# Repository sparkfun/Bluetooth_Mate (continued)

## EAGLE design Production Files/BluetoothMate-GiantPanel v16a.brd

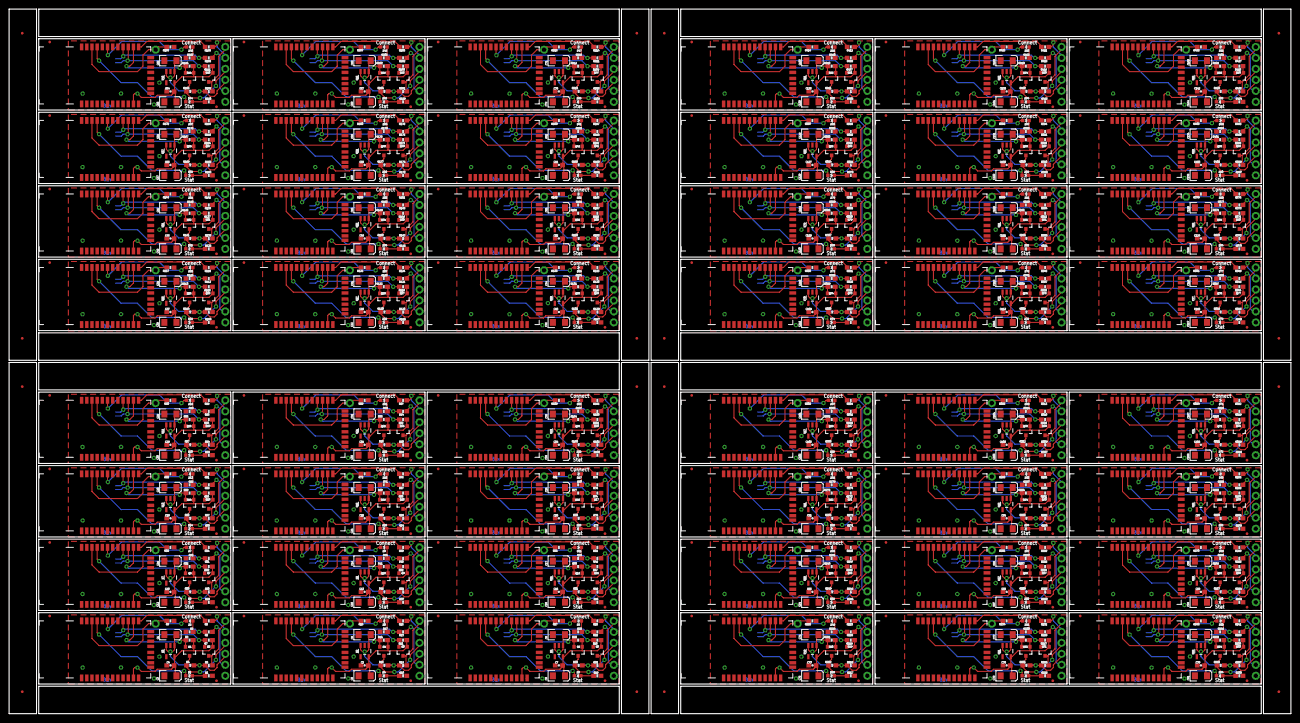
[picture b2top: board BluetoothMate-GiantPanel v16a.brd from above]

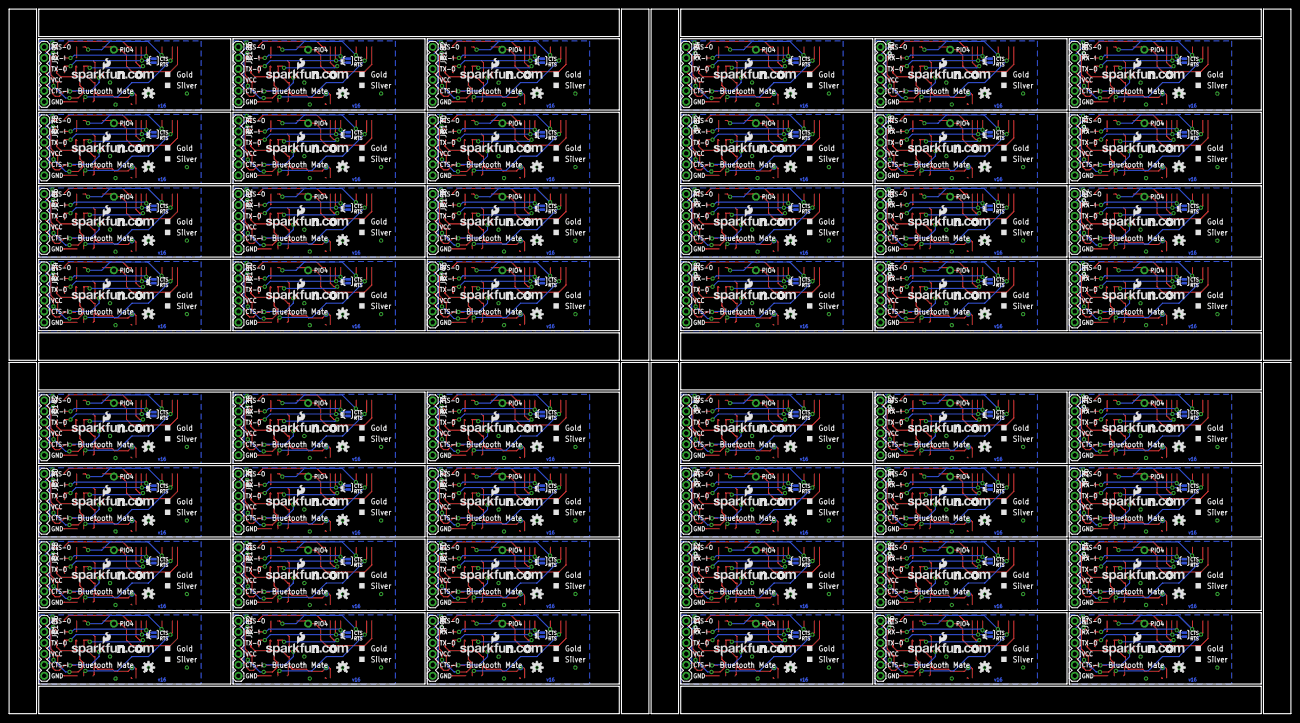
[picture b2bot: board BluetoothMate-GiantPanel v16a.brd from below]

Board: 2 copper layers, 296.7 x 163.1 mm, 1264 parts (240 on the bottom side), 768 nets.

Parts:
C1, C3, C5, C6, C8, C9, C11, C12, C14, C15, C17, C18, C20, C21, C23, C24, C26, C27, C29, C30, C32, C33, C35, C36, C38, C39, C41, C42, C44, C45, C47, C48, C50, C51, C53, C54, C56, C57, C59, C60, C62, C63, C65, C66, C68, C69, C71, C72, C74, C75, C77, C78, C80, C81, C83, C84, C86, C87, C89, C90, C92, C93, C95, C96, C98, C99, C101, C102, C104, C105, C107, C108, C110, C111, C113, C114, C116, C117, C119, C120, C122, C123, C125, C126, C128, C129, C131, C132, C134, C135, C137, C138, C140, C141, C143, C144: 10uF; EIA3216
C2, C4, C7, C10, C13, C16, C19, C22, C25, C28, C31, C34, C37, C40, C43, C46, C49, C52, C55, C58, C61, C64, C67, C70, C73, C76, C79, C82, C85, C88, C91, C94, C97, C100, C103, C106, C109, C112, C115, C118, C121, C124, C127, C130, C133, C136, C139, C142: 1uF; 0603-CAP
D1, D4, D6, D8, D10, D12, D14, D16, D18, D20, D22, D24, D26, D28, D30, D32, D34, D36, D38, D40, D42, D44, D46, D48, D50, D52, D54, D56, D58, D60, D62, D64, D66, D68, D70, D72, D74, D76, D78, D80, D82, D84, D86, D88, D90, D92, D94, D96: Red; LED-0603
D2, D3, D5, D7, D9, D11, D13, D15, D17, D19, D21, D23, D25, D27, D29, D31, D33, D35, D37, D39, D41, D43, D45, D47, D49, D51, D53, D55, D57, D59, D61, D63, D65, D67, D69, D71, D73, D75, D77, D79, D81, D83, D85, D87, D89, D91, D93, D95: Green; LED-0603
E$1, E$2, E$3, E$4, E$5, E$6, E$7, E$8, E$9, E$10, E$11, E$12, E$13, E$14, E$15, E$16: MICRO-FIDUCIAL
JP1, JP4, JP7, JP8, JP11, JP12, JP15, JP16, JP19, JP20, JP23, JP24, JP27, JP28, JP31, JP32, JP35, JP36, JP39, JP40, JP43, JP44, JP47, JP48, JP51, JP52, JP55, JP56, JP59, JP60, JP63, JP64, JP67, JP68, JP71, JP72, JP75, JP76, JP79, JP80, JP83, JP84, JP87, JP88, JP91, JP92, JP95, JP96, JP99, JP100, JP103, JP104, JP107, JP108, JP111, JP112, JP115, JP116, JP119, JP120, JP123, JP124, JP127, JP128, JP131, JP132, JP135, JP136, JP139, JP140, JP143, JP144, JP147, JP148, JP151, JP152, JP155, JP156, JP159, JP160, JP163, JP164, JP167, JP168, JP171, JP172, JP175, JP176, JP179, JP180, JP183, JP184, JP187, JP188, JP191, JP192: FIDUCIAL1X2.5; FIDUCIAL-1X2.5
JP2, JP5, JP9, JP13, JP17, JP21, JP25, JP29, JP33, JP37, JP41, JP45, JP49, JP53, JP57, JP61, JP65, JP69, JP73, JP77, JP81, JP85, JP89, JP93, JP97, JP101, JP105, JP109, JP113, JP117, JP121, JP125, JP129, JP133, JP137, JP141, JP145, JP149, JP153, JP157, JP161, JP165, JP169, JP173, JP177, JP181, JP185, JP189: M01SMDNS; 1X01NS
JP3, JP6, JP10, JP14, JP18, JP22, JP26, JP30, JP34, JP38, JP42, JP46, JP50, JP54, JP58, JP62, JP66, JP70, JP74, JP78, JP82, JP86, JP90, JP94, JP98, JP102, JP106, JP110, JP114, JP118, JP122, JP126, JP130, JP134, JP138, JP142, JP146, JP150, JP154, JP158, JP162, JP166, JP170, JP174, JP178, JP182, JP186, JP190: 1X06
LOGO1, LOGO2, LOGO3, LOGO4, LOGO5, LOGO6, LOGO7, LOGO8, LOGO9, LOGO10, LOGO11, LOGO12, LOGO13, LOGO14, LOGO15, LOGO16, LOGO17, LOGO18, LOGO19, LOGO20, LOGO21, LOGO22, LOGO23, LOGO24, LOGO25, LOGO26, LOGO27, LOGO28, LOGO29, LOGO30, LOGO31, LOGO32, LOGO33, LOGO34, LOGO35, LOGO36, LOGO37, LOGO38, LOGO39, LOGO40, LOGO41, LOGO42, LOGO43, LOGO44, LOGO45, LOGO46, LOGO47, LOGO48: OSHW-LOGOS; OSHW-LOGO-S
Q1, Q2, Q3, Q4, Q5, Q6, Q7, Q8, Q9, Q10, Q11, Q12, Q13, Q14, Q15, Q16, Q17, Q18, Q19, Q20, Q21, Q22, Q23, Q24, Q25, Q26, Q27, Q28, Q29, Q30, Q31, Q32, Q33, Q34, Q35, Q36, Q37, Q38, Q39, Q40, Q41, Q42, Q43, Q44, Q45, Q46, Q47, Q48, Q49, Q50, Q51, Q52, Q53, Q54, Q55, Q56, Q57, Q58, Q59, Q60, Q61, Q62, Q63, Q64, Q65, Q66, Q67, Q68, Q69, Q70, Q71, Q72, Q73, Q74, Q75, Q76, Q77, Q78, Q79, Q80, Q81, Q82, Q83, Q84, Q85, Q86, Q87, Q88, Q89, Q90, Q91, Q92, Q93, Q94, Q95, Q96: MOSFET-NCHANNELSMD; SOT23-3
R1, R6, R10, R17, R19, R26, R28, R35, R37, R44, R46, R53, R55, R62, R64, R71, R73, R80, R82, R89, R91, R98, R100, R107, R109, R116, R118, R125, R127, R134, R136, R143, R145, R152, R154, R161, R163, R170, R172, R179, R181, R188, R190, R197, R199, R206, R208, R215, R217, R224, R226, R233, R235, R242, R244, R251, R253, R260, R262, R269, R271, R278, R280, R287, R289, R296, R298, R305, R307, R314, R316, R323, R325, R332, R334, R341, R343, R350, R352, R359, R361, R368, R370, R377, R379, R386, R388, R395, R397, R404, R406, R413, R415, R422, R424, R431: 330; 0603-RES
R2, R3, R4, R5, R7, R8, R9, R11, R12, R13, R14, R15, R16, R18, R20, R21, R22, R23, R24, R25, R27, R29, R30, R31, R32, R33, R34, R36, R38, R39, R40, R41, R42, R43, R45, R47, R48, R49, R50, R51, R52, R54, R56, R57, R58, R59, R60, R61, R63, R65, R66, R67, R68, R69, R70, R72, R74, R75, R76, R77, R78, R79, R81, R83, R84, R85, R86, R87, R88, R90, R92, R93, R94, R95, R96, R97, R99, R101, R102, R103, R104, R105, R106, R108, R110, R111, R112, R113, R114, R115, R117, R119, R120, R121, R122, R123, R124, R126, R128, R129, R130, R131, R132, R133, R135, R137, R138, R139, R140, R141, R142, R144, R146, R147, R148, R149, R150, R151, R153, R155, R156, R157, R158, R159, R160, R162, R164, R165, R166, R167, R168, R169, R171, R173, R174, R175, R176, R177, R178, R180, R182, R183, R184, R185, R186, R187, R189, R191, R192, R193, R194, R195, R196, R198, R200, R201, R202, R203, R204, R205, R207, R209, R210, R211, R212, R213, R214, R216, R218, R219, R220, R221, R222, R223, R225, R227, R228, R229, R230, R231, R232, R234, R236, R237, R238, R239, R240, R241, R243, R245, R246, R247, R248, R249, R250, R252, R254, R255, R256, R257, R258, R259, R261, R263, R264, R265, R266, R267, R268, R270, R272, R273, R274, R275, R276, R277, R279, R281, R282, R283, R284, R285, R286, R288, R290, R291, R292, R293, R294, R295, R297, R299, R300, R301, R302, R303, R304, R306, R308, R309, R310, R311, R312, R313, R315, R317, R318, R319, R320, R321, R322, R324, R326, R327, R328, R329, R330, R331, R333, R335, R336, R337, R338, R339, R340, R342, R344, R345, R346, R347, R348, R349, R351, R353, R354, R355, R356, R357, R358, R360, R362, R363, R364, R365, R366, R367, R369, R371, R372, R373, R374, R375, R376, R378, R380, R381, R382, R383, R384, R385, R387, R389, R390, R391, R392, R393, R394, R396, R398, R399, R400, R401, R402, R403, R405, R407, R408, R409, R410, R411, R412, R414, R416, R417, R418, R419, R420, R421, R423, R425, R426, R427, R428, R429, R430, R432: 10K; 0603-RES
SJ1, SJ2, SJ3, SJ4, SJ5, SJ6, SJ7, SJ8, SJ9, SJ10, SJ11, SJ12, SJ13, SJ14, SJ15, SJ16, SJ17, SJ18, SJ19, SJ20, SJ21, SJ22, SJ23, SJ24, SJ25, SJ26, SJ27, SJ28, SJ29, SJ30, SJ31, SJ32, SJ33, SJ34, SJ35, SJ36, SJ37, SJ38, SJ39, SJ40, SJ41, SJ42, SJ43, SJ44, SJ45, SJ46, SJ47, SJ48: SOLDERJUMPERNO; SJ_2S-NO
TP1, TP2, TP3, TP4, TP5, TP6, TP7, TP8, TP9, TP10, TP11, TP12, TP13, TP14, TP15, TP16, TP17, TP18, TP19, TP20, TP21, TP22, TP23, TP24, TP25, TP26, TP27, TP28, TP29, TP30, TP31, TP32, TP33, TP34, TP35, TP36, TP37, TP38, TP39, TP40, TP41, TP42, TP43, TP44, TP45, TP46, TP47, TP48: PAD.03X.05
U1, U4, U6, U8, U10, U12, U14, U16, U18, U20, U22, U24, U26, U28, U30, U32, U34, U36, U38, U40, U42, U44, U46, U48, U50, U52, U54, U56, U58, U60, U62, U64, U66, U68, U70, U72, U74, U76, U78, U80, U82, U84, U86, U88, U90, U92, U94, U96: BLUETOOTH-RN41; RN41
U2, U3, U5, U7, U9, U11, U13, U15, U17, U19, U21, U23, U25, U27, U29, U31, U33, U35, U37, U39, U41, U43, U45, U47, U49, U51, U53, U55, U57, U59, U61, U63, U65, U67, U69, U71, U73, U75, U77, U79, U81, U83, U85, U87, U89, U91, U93, U95: V_REG_LDOSMD; SOT23-5
U$1, U$2, U$3, U$4, U$5, U$6, U$7, U$8, U$9, U$10, U$11, U$12, U$13, U$14, U$15, U$16, U$17, U$18, U$19, U$20, U$21, U$22, U$23, U$24, U$25, U$26, U$27, U$28, U$29, U$30, U$31, U$32, U$33, U$34, U$35, U$36, U$37, U$38, U$39, U$40, U$41, U$42, U$43, U$44, U$45, U$46, U$47, U$48: LOGO-SFENEW; SFE-NEW-WEBLOGO

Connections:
3.3V: C3.A, C4.1, Q1.1, Q2.1, R3.1, R7.1, TP1.P$1, U1.11, U3.5
3.3V1: C2.1, C6.A, Q3.1, Q4.1, R11.1, R14.1, TP2.P$1, U2.5, U4.11
3.3V2: C7.1, C9.A, Q5.1, Q6.1, R20.1, R23.1, TP3.P$1, U5.5, U6.11
3.3V3: C10.1, C12.A, Q7.1, Q8.1, R29.1, R32.1, TP4.P$1, U7.5, U8.11
3.3V4: C13.1, C15.A, Q9.1, Q10.1, R38.1, R41.1, TP5.P$1, U9.5, U10.11
3.3V5: C16.1, C18.A, Q11.1, Q12.1, R47.1, R50.1, TP6.P$1, U11.5, U12.11
3.3V6: C19.1, C21.A, Q13.1, Q14.1, R56.1, R59.1, TP7.P$1, U13.5, U14.11
3.3V7: C22.1, C24.A, Q15.1, Q16.1, R65.1, R68.1, TP8.P$1, U15.5, U16.11
3.3V8: C25.1, C27.A, Q17.1, Q18.1, R74.1, R77.1, TP9.P$1, U17.5, U18.11
3.3V9: C28.1, C30.A, Q19.1, Q20.1, R83.1, R86.1, TP10.P$1, U19.5, U20.11
3.3V10: C31.1, C33.A, Q21.1, Q22.1, R92.1, R95.1, TP11.P$1, U21.5, U22.11
3.3V11: C34.1, C36.A, Q23.1, Q24.1, R101.1, R104.1, TP12.P$1, U23.5, U24.11
3.3V12: C37.1, C39.A, Q25.1, Q26.1, R110.1, R113.1, TP13.P$1, U25.5, U26.11
3.3V13: C40.1, C42.A, Q27.1, Q28.1, R119.1, R122.1, TP14.P$1, U27.5, U28.11
3.3V14: C43.1, C45.A, Q29.1, Q30.1, R128.1, R131.1, TP15.P$1, U29.5, U30.11
3.3V15: C46.1, C48.A, Q31.1, Q32.1, R137.1, R140.1, TP16.P$1, U31.5, U32.11
3.3V16: C49.1, C51.A, Q33.1, Q34.1, R146.1, R149.1, TP17.P$1, U33.5, U34.11
3.3V17: C52.1, C54.A, Q35.1, Q36.1, R155.1, R158.1, TP18.P$1, U35.5, U36.11
3.3V18: C55.1, C57.A, Q37.1, Q38.1, R164.1, R167.1, TP19.P$1, U37.5, U38.11
3.3V19: C58.1, C60.A, Q39.1, Q40.1, R173.1, R176.1, TP20.P$1, U39.5, U40.11
3.3V20: C61.1, C63.A, Q41.1, Q42.1, R182.1, R185.1, TP21.P$1, U41.5, U42.11
3.3V21: C64.1, C66.A, Q43.1, Q44.1, R191.1, R194.1, TP22.P$1, U43.5, U44.11
3.3V22: C67.1, C69.A, Q45.1, Q46.1, R200.1, R203.1, TP23.P$1, U45.5, U46.11
3.3V23: C70.1, C72.A, Q47.1, Q48.1, R209.1, R212.1, TP24.P$1, U47.5, U48.11
3.3V24: C73.1, C75.A, Q49.1, Q50.1, R218.1, R221.1, TP25.P$1, U49.5, U50.11
3.3V25: C76.1, C78.A, Q51.1, Q52.1, R227.1, R230.1, TP26.P$1, U51.5, U52.11
3.3V26: C79.1, C81.A, Q53.1, Q54.1, R236.1, R239.1, TP27.P$1, U53.5, U54.11
3.3V27: C82.1, C84.A, Q55.1, Q56.1, R245.1, R248.1, TP28.P$1, U55.5, U56.11
3.3V28: C85.1, C87.A, Q57.1, Q58.1, R254.1, R257.1, TP29.P$1, U57.5, U58.11
3.3V29: C88.1, C90.A, Q59.1, Q60.1, R263.1, R266.1, TP30.P$1, U59.5, U60.11
3.3V30: C91.1, C93.A, Q61.1, Q62.1, R272.1, R275.1, TP31.P$1, U61.5, U62.11
3.3V31: C94.1, C96.A, Q63.1, Q64.1, R281.1, R284.1, TP32.P$1, U63.5, U64.11
3.3V32: C97.1, C99.A, Q65.1, Q66.1, R290.1, R293.1, TP33.P$1, U65.5, U66.11
3.3V33: C100.1, C102.A, Q67.1, Q68.1, R299.1, R302.1, TP34.P$1, U67.5, U68.11
3.3V34: C103.1, C105.A, Q69.1, Q70.1, R308.1, R311.1, TP35.P$1, U69.5, U70.11
3.3V35: C106.1, C108.A, Q71.1, Q72.1, R317.1, R320.1, TP36.P$1, U71.5, U72.11
3.3V36: C109.1, C111.A, Q73.1, Q74.1, R326.1, R329.1, TP37.P$1, U73.5, U74.11
3.3V37: C112.1, C114.A, Q75.1, Q76.1, R335.1, R338.1, TP38.P$1, U75.5, U76.11
3.3V38: C115.1, C117.A, Q77.1, Q78.1, R344.1, R347.1, TP39.P$1, U77.5, U78.11
3.3V39: C118.1, C120.A, Q79.1, Q80.1, R353.1, R356.1, TP40.P$1, U79.5, U80.11
3.3V40: C121.1, C123.A, Q81.1, Q82.1, R362.1, R365.1, TP41.P$1, U81.5, U82.11
3.3V41: C124.1, C126.A, Q83.1, Q84.1, R371.1, R374.1, TP42.P$1, U83.5, U84.11
3.3V42: C127.1, C129.A, Q85.1, Q86.1, R380.1, R383.1, TP43.P$1, U85.5, U86.11
3.3V43: C130.1, C132.A, Q87.1, Q88.1, R389.1, R392.1, TP44.P$1, U87.5, U88.11
3.3V44: C133.1, C135.A, Q89.1, Q90.1, R398.1, R401.1, TP45.P$1, U89.5, U90.11
3.3V45: C136.1, C138.A, Q91.1, Q92.1, R407.1, R410.1, TP46.P$1, U91.5, U92.11
3.3V46: C139.1, C141.A, Q93.1, Q94.1, R416.1, R419.1, TP47.P$1, U93.5, U94.11
3.3V47: C142.1, C144.A, Q95.1, Q96.1, R425.1, R428.1, TP48.P$1, U95.5, U96.11
CTS: R2.1, SJ1.2, U1.16
CTS1: R13.1, SJ2.2, U4.16
CTS2: R22.1, SJ3.2, U6.16
CTS3: R31.1, SJ4.2, U8.16
CTS4: R40.1, SJ5.2, U10.16
CTS5: R49.1, SJ6.2, U12.16
CTS6: R58.1, SJ7.2, U14.16
CTS7: R67.1, SJ8.2, U16.16
CTS8: R76.1, SJ9.2, U18.16
CTS9: R85.1, SJ10.2, U20.16
CTS10: R94.1, SJ11.2, U22.16
CTS11: R103.1, SJ12.2, U24.16
CTS12: R112.1, SJ13.2, U26.16
CTS13: R121.1, SJ14.2, U28.16
CTS14: R130.1, SJ15.2, U30.16
CTS15: R139.1, SJ16.2, U32.16
CTS16: R148.1, SJ17.2, U34.16
CTS17: R157.1, SJ18.2, U36.16
CTS18: R166.1, SJ19.2, U38.16
CTS19: R175.1, SJ20.2, U40.16
CTS20: R184.1, SJ21.2, U42.16
CTS21: R193.1, SJ22.2, U44.16
CTS22: R202.1, SJ23.2, U46.16
CTS23: R211.1, SJ24.2, U48.16
CTS24: R220.1, SJ25.2, U50.16
CTS25: R229.1, SJ26.2, U52.16
CTS26: R238.1, SJ27.2, U54.16
CTS27: R247.1, SJ28.2, U56.16
CTS28: R256.1, SJ29.2, U58.16
CTS29: R265.1, SJ30.2, U60.16
CTS30: R274.1, SJ31.2, U62.16
CTS31: R283.1, SJ32.2, U64.16
CTS32: R292.1, SJ33.2, U66.16
CTS33: R301.1, SJ34.2, U68.16
CTS34: R310.1, SJ35.2, U70.16
CTS35: R319.1, SJ36.2, U72.16
CTS36: R328.1, SJ37.2, U74.16
CTS37: R337.1, SJ38.2, U76.16
CTS38: R346.1, SJ39.2, U78.16
CTS39: R355.1, SJ40.2, U80.16
CTS40: R364.1, SJ41.2, U82.16
CTS41: R373.1, SJ42.2, U84.16
CTS42: R382.1, SJ43.2, U86.16
CTS43: R391.1, SJ44.2, U88.16
CTS44: R400.1, SJ45.2, U90.16
CTS45: R409.1, SJ46.2, U92.16
CTS46: R418.1, SJ47.2, U94.16
CTS47: R427.1, SJ48.2, U96.16
CTS_5V: JP3.5, R2.2
CTS_5V1: JP6.5, R13.2
CTS_5V2: JP10.5, R22.2
CTS_5V3: JP14.5, R31.2
CTS_5V4: JP18.5, R40.2
CTS_5V5: JP22.5, R49.2
CTS_5V6: JP26.5, R58.2
CTS_5V7: JP30.5, R67.2
CTS_5V8: JP34.5, R76.2
CTS_5V9: JP38.5, R85.2
CTS_5V10: JP42.5, R94.2
CTS_5V11: JP46.5, R103.2
CTS_5V12: JP50.5, R112.2
CTS_5V13: JP54.5, R121.2
CTS_5V14: JP58.5, R130.2
CTS_5V15: JP62.5, R139.2
CTS_5V16: JP66.5, R148.2
CTS_5V17: JP70.5, R157.2
CTS_5V18: JP74.5, R166.2
CTS_5V19: JP78.5, R175.2
CTS_5V20: JP82.5, R184.2
CTS_5V21: JP86.5, R193.2
CTS_5V22: JP90.5, R202.2
CTS_5V23: JP94.5, R211.2
CTS_5V24: JP98.5, R220.2
CTS_5V25: JP102.5, R229.2
CTS_5V26: JP106.5, R238.2
CTS_5V27: JP110.5, R247.2
CTS_5V28: JP114.5, R256.2
CTS_5V29: JP118.5, R265.2
CTS_5V30: JP122.5, R274.2
CTS_5V31: JP126.5, R283.2
CTS_5V32: JP130.5, R292.2
CTS_5V33: JP134.5, R301.2
CTS_5V34: JP138.5, R310.2
CTS_5V35: JP142.5, R319.2
CTS_5V36: JP146.5, R328.2
CTS_5V37: JP150.5, R337.2
CTS_5V38: JP154.5, R346.2
CTS_5V39: JP158.5, R355.2
CTS_5V40: JP162.5, R364.2
CTS_5V41: JP166.5, R373.2
CTS_5V42: JP170.5, R382.2
CTS_5V43: JP174.5, R391.2
CTS_5V44: JP178.5, R400.2
CTS_5V45: JP182.5, R409.2
CTS_5V46: JP186.5, R418.2
CTS_5V47: JP190.5, R427.2
D1: D1.C, R1.1
D2: D2.C, R6.1
D3: D4.C, R10.1
D4: D3.C, R17.1
D5: D6.C, R19.1
D6: D5.C, R26.1
D7: D8.C, R28.1
D8: D7.C, R35.1
D9: D10.C, R37.1
D10: D9.C, R44.1
D11: D12.C, R46.1
D12: D11.C, R53.1
D13: D14.C, R55.1
D14: D13.C, R62.1
D15: D16.C, R64.1
D16: D15.C, R71.1
D17: D18.C, R73.1
D18: D17.C, R80.1
D19: D20.C, R82.1
D20: D19.C, R89.1
D21: D22.C, R91.1
D22: D21.C, R98.1
D23: D24.C, R100.1
D24: D23.C, R107.1
D25: D26.C, R109.1
D26: D25.C, R116.1
D27: D28.C, R118.1
D28: D27.C, R125.1
D29: D30.C, R127.1
D30: D29.C, R134.1
D31: D32.C, R136.1
D32: D31.C, R143.1
D33: D34.C, R145.1
D34: D33.C, R152.1
D35: D36.C, R154.1
D36: D35.C, R161.1
D37: D38.C, R163.1
D38: D37.C, R170.1
D39: D40.C, R172.1
D40: D39.C, R179.1
D41: D42.C, R181.1
D42: D41.C, R188.1
D43: D44.C, R190.1
D44: D43.C, R197.1
D45: D46.C, R199.1
D46: D45.C, R206.1
D47: D48.C, R208.1
D48: D47.C, R215.1
D49: D50.C, R217.1
D50: D49.C, R224.1
D51: D52.C, R226.1
D52: D51.C, R233.1
D53: D54.C, R235.1
D54: D53.C, R242.1
D55: D56.C, R244.1
D56: D55.C, R251.1
D57: D58.C, R253.1
D58: D57.C, R260.1
D59: D60.C, R262.1
D60: D59.C, R269.1
D61: D62.C, R271.1
D62: D61.C, R278.1
D63: D64.C, R280.1
D64: D63.C, R287.1
D65: D66.C, R289.1
D66: D65.C, R296.1
D67: D68.C, R298.1
D68: D67.C, R305.1
D69: D70.C, R307.1
D70: D69.C, R314.1
D71: D72.C, R316.1
D72: D71.C, R323.1
D73: D74.C, R325.1
D74: D73.C, R332.1
D75: D76.C, R334.1
D76: D75.C, R341.1
D77: D78.C, R343.1
D78: D77.C, R350.1
D79: D80.C, R352.1
D80: D79.C, R359.1
D81: D82.C, R361.1
D82: D81.C, R368.1
D83: D84.C, R370.1
D84: D83.C, R377.1
D85: D86.C, R379.1
D86: D85.C, R386.1
D87: D88.C, R388.1
D88: D87.C, R395.1
D89: D90.C, R397.1
D90: D89.C, R404.1
D91: D92.C, R406.1
D92: D91.C, R413.1
D93: D94.C, R415.1
D94: D93.C, R422.1
D95: D96.C, R424.1
D96: D95.C, R431.1
GND: C1.C, C3.C, C4.2, JP3.6, R1.2, R6.2, R9.1, U1.1, U1.12, U1.28, U1.29, U3.2
GND1: C2.2, C5.C, C6.C, JP6.6, R10.2, R17.2, R18.1, U2.2, U4.1, U4.12, U4.28, U4.29
GND2: C7.2, C8.C, C9.C, JP10.6, R19.2, R26.2, R27.1, U5.2, U6.1, U6.12, U6.28, U6.29
GND3: C10.2, C11.C, C12.C, JP14.6, R28.2, R35.2, R36.1, U7.2, U8.1, U8.12, U8.28, U8.29
GND4: C13.2, C14.C, C15.C, JP18.6, R37.2, R44.2, R45.1, U9.2, U10.1, U10.12, U10.28, U10.29
GND5: C16.2, C17.C, C18.C, JP22.6, R46.2, R53.2, R54.1, U11.2, U12.1, U12.12, U12.28, U12.29
GND6: C19.2, C20.C, C21.C, JP26.6, R55.2, R62.2, R63.1, U13.2, U14.1, U14.12, U14.28, U14.29
GND7: C22.2, C23.C, C24.C, JP30.6, R64.2, R71.2, R72.1, U15.2, U16.1, U16.12, U16.28, U16.29
GND8: C25.2, C26.C, C27.C, JP34.6, R73.2, R80.2, R81.1, U17.2, U18.1, U18.12, U18.28, U18.29
GND9: C28.2, C29.C, C30.C, JP38.6, R82.2, R89.2, R90.1, U19.2, U20.1, U20.12, U20.28, U20.29
GND10: C31.2, C32.C, C33.C, JP42.6, R91.2, R98.2, R99.1, U21.2, U22.1, U22.12, U22.28, U22.29
GND11: C34.2, C35.C, C36.C, JP46.6, R100.2, R107.2, R108.1, U23.2, U24.1, U24.12, U24.28, U24.29
GND12: C37.2, C38.C, C39.C, JP50.6, R109.2, R116.2, R117.1, U25.2, U26.1, U26.12, U26.28, U26.29
GND13: C40.2, C41.C, C42.C, JP54.6, R118.2, R125.2, R126.1, U27.2, U28.1, U28.12, U28.28, U28.29
GND14: C43.2, C44.C, C45.C, JP58.6, R127.2, R134.2, R135.1, U29.2, U30.1, U30.12, U30.28, U30.29
GND15: C46.2, C47.C, C48.C, JP62.6, R136.2, R143.2, R144.1, U31.2, U32.1, U32.12, U32.28, U32.29
GND16: C49.2, C50.C, C51.C, JP66.6, R145.2, R152.2, R153.1, U33.2, U34.1, U34.12, U34.28, U34.29
GND17: C52.2, C53.C, C54.C, JP70.6, R154.2, R161.2, R162.1, U35.2, U36.1, U36.12, U36.28, U36.29
GND18: C55.2, C56.C, C57.C, JP74.6, R163.2, R170.2, R171.1, U37.2, U38.1, U38.12, U38.28, U38.29
GND19: C58.2, C59.C, C60.C, JP78.6, R172.2, R179.2, R180.1, U39.2, U40.1, U40.12, U40.28, U40.29
GND20: C61.2, C62.C, C63.C, JP82.6, R181.2, R188.2, R189.1, U41.2, U42.1, U42.12, U42.28, U42.29
GND21: C64.2, C65.C, C66.C, JP86.6, R190.2, R197.2, R198.1, U43.2, U44.1, U44.12, U44.28, U44.29
GND22: C67.2, C68.C, C69.C, JP90.6, R199.2, R206.2, R207.1, U45.2, U46.1, U46.12, U46.28, U46.29
GND23: C70.2, C71.C, C72.C, JP94.6, R208.2, R215.2, R216.1, U47.2, U48.1, U48.12, U48.28, U48.29
GND24: C73.2, C74.C, C75.C, JP98.6, R217.2, R224.2, R225.1, U49.2, U50.1, U50.12, U50.28, U50.29
GND25: C76.2, C77.C, C78.C, JP102.6, R226.2, R233.2, R234.1, U51.2, U52.1, U52.12, U52.28, U52.29
GND26: C79.2, C80.C, C81.C, JP106.6, R235.2, R242.2, R243.1, U53.2, U54.1, U54.12, U54.28, U54.29
GND27: C82.2, C83.C, C84.C, JP110.6, R244.2, R251.2, R252.1, U55.2, U56.1, U56.12, U56.28, U56.29
GND28: C85.2, C86.C, C87.C, JP114.6, R253.2, R260.2, R261.1, U57.2, U58.1, U58.12, U58.28, U58.29
GND29: C88.2, C89.C, C90.C, JP118.6, R262.2, R269.2, R270.1, U59.2, U60.1, U60.12, U60.28, U60.29
GND30: C91.2, C92.C, C93.C, JP122.6, R271.2, R278.2, R279.1, U61.2, U62.1, U62.12, U62.28, U62.29
GND31: C94.2, C95.C, C96.C, JP126.6, R280.2, R287.2, R288.1, U63.2, U64.1, U64.12, U64.28, U64.29
GND32: C97.2, C98.C, C99.C, JP130.6, R289.2, R296.2, R297.1, U65.2, U66.1, U66.12, U66.28, U66.29
GND33: C100.2, C101.C, C102.C, JP134.6, R298.2, R305.2, R306.1, U67.2, U68.1, U68.12, U68.28, U68.29
GND34: C103.2, C104.C, C105.C, JP138.6, R307.2, R314.2, R315.1, U69.2, U70.1, U70.12, U70.28, U70.29
GND35: C106.2, C107.C, C108.C, JP142.6, R316.2, R323.2, R324.1, U71.2, U72.1, U72.12, U72.28, U72.29
GND36: C109.2, C110.C, C111.C, JP146.6, R325.2, R332.2, R333.1, U73.2, U74.1, U74.12, U74.28, U74.29
GND37: C112.2, C113.C, C114.C, JP150.6, R334.2, R341.2, R342.1, U75.2, U76.1, U76.12, U76.28, U76.29
GND38: C115.2, C116.C, C117.C, JP154.6, R343.2, R350.2, R351.1, U77.2, U78.1, U78.12, U78.28, U78.29
GND39: C118.2, C119.C, C120.C, JP158.6, R352.2, R359.2, R360.1, U79.2, U80.1, U80.12, U80.28, U80.29
GND40: C121.2, C122.C, C123.C, JP162.6, R361.2, R368.2, R369.1, U81.2, U82.1, U82.12, U82.28, U82.29
GND41: C124.2, C125.C, C126.C, JP166.6, R370.2, R377.2, R378.1, U83.2, U84.1, U84.12, U84.28, U84.29
GND42: C127.2, C128.C, C129.C, JP170.6, R379.2, R386.2, R387.1, U85.2, U86.1, U86.12, U86.28, U86.29
GND43: C130.2, C131.C, C132.C, JP174.6, R388.2, R395.2, R396.1, U87.2, U88.1, U88.12, U88.28, U88.29
GND44: C133.2, C134.C, C135.C, JP178.6, R397.2, R404.2, R405.1, U89.2, U90.1, U90.12, U90.28, U90.29
GND45: C136.2, C137.C, C138.C, JP182.6, R406.2, R413.2, R414.1, U91.2, U92.1, U92.12, U92.28, U92.29
GND46: C139.2, C140.C, C141.C, JP186.6, R415.2, R422.2, R423.1, U93.2, U94.1, U94.12, U94.28, U94.29
GND47: C142.2, C143.C, C144.C, JP190.6, R424.2, R431.2, R432.1, U95.2, U96.1, U96.12, U96.28, U96.29
unnamed: D1.A, U1.21
unnamed: D2.A, U1.19
unnamed: D4.A, U4.21
unnamed: D3.A, U4.19
unnamed: D6.A, U6.21
unnamed: D5.A, U6.19
unnamed: D8.A, U8.21
unnamed: D7.A, U8.19
unnamed: D10.A, U10.21
unnamed: D9.A, U10.19
unnamed: D12.A, U12.21
unnamed: D11.A, U12.19
unnamed: D14.A, U14.21
unnamed: D13.A, U14.19
unnamed: D16.A, U16.21
unnamed: D15.A, U16.19
unnamed: D18.A, U18.21
unnamed: D17.A, U18.19
unnamed: D20.A, U20.21
unnamed: D19.A, U20.19
unnamed: D22.A, U22.21
unnamed: D21.A, U22.19
unnamed: D24.A, U24.21
unnamed: D23.A, U24.19
unnamed: D26.A, U26.21
unnamed: D25.A, U26.19
unnamed: D28.A, U28.21
unnamed: D27.A, U28.19
unnamed: D30.A, U30.21
unnamed: D29.A, U30.19
unnamed: D32.A, U32.21
unnamed: D31.A, U32.19
unnamed: D34.A, U34.21
unnamed: D33.A, U34.19
unnamed: D36.A, U36.21
unnamed: D35.A, U36.19
unnamed: D38.A, U38.21
unnamed: D37.A, U38.19
unnamed: D40.A, U40.21
unnamed: D39.A, U40.19
unnamed: D42.A, U42.21
unnamed: D41.A, U42.19
unnamed: D44.A, U44.21
unnamed: D43.A, U44.19
unnamed: D46.A, U46.21
unnamed: D45.A, U46.19
unnamed: D48.A, U48.21
unnamed: D47.A, U48.19
unnamed: D50.A, U50.21
unnamed: D49.A, U50.19
unnamed: D52.A, U52.21
unnamed: D51.A, U52.19
unnamed: D54.A, U54.21
unnamed: D53.A, U54.19
unnamed: D56.A, U56.21
unnamed: D55.A, U56.19
unnamed: D58.A, U58.21
unnamed: D57.A, U58.19
unnamed: D60.A, U60.21
unnamed: D59.A, U60.19
unnamed: D62.A, U62.21
unnamed: D61.A, U62.19
unnamed: D64.A, U64.21
unnamed: D63.A, U64.19
unnamed: D66.A, U66.21
unnamed: D65.A, U66.19
unnamed: D68.A, U68.21
unnamed: D67.A, U68.19
unnamed: D70.A, U70.21
unnamed: D69.A, U70.19
unnamed: D72.A, U72.21
unnamed: D71.A, U72.19
unnamed: D74.A, U74.21
unnamed: D73.A, U74.19
unnamed: D76.A, U76.21
unnamed: D75.A, U76.19
unnamed: D78.A, U78.21
unnamed: D77.A, U78.19
unnamed: D80.A, U80.21
unnamed: D79.A, U80.19
unnamed: D82.A, U82.21
unnamed: D81.A, U82.19
unnamed: D84.A, U84.21
unnamed: D83.A, U84.19
unnamed: D86.A, U86.21
unnamed: D85.A, U86.19
unnamed: D88.A, U88.21
unnamed: D87.A, U88.19
unnamed: D90.A, U90.21
unnamed: D89.A, U90.19
unnamed: D92.A, U92.21
unnamed: D91.A, U92.19
unnamed: D94.A, U94.21
unnamed: D93.A, U94.19
unnamed: D96.A, U96.21
unnamed: D95.A, U96.19
PIO1: JP5.1, R18.2, U4.22
PIO2: JP9.1, R27.2, U6.22
PIO3: JP13.1, R36.2, U8.22
PIO4: JP2.1, R9.2, U1.22
PIO5: JP17.1, R45.2, U10.22
PIO6: JP21.1, R54.2, U12.22
PIO7: JP25.1, R63.2, U14.22
PIO8: JP29.1, R72.2, U16.22
PIO9: JP33.1, R81.2, U18.22
PIO10: JP37.1, R90.2, U20.22
PIO11: JP41.1, R99.2, U22.22
PIO12: JP45.1, R108.2, U24.22
PIO13: JP49.1, R117.2, U26.22
PIO14: JP53.1, R126.2, U28.22
PIO15: JP57.1, R135.2, U30.22
PIO16: JP61.1, R144.2, U32.22
PIO17: JP65.1, R153.2, U34.22
PIO18: JP69.1, R162.2, U36.22
PIO19: JP73.1, R171.2, U38.22
PIO20: JP77.1, R180.2, U40.22
PIO21: JP81.1, R189.2, U42.22
PIO22: JP85.1, R198.2, U44.22
PIO23: JP89.1, R207.2, U46.22
PIO24: JP93.1, R216.2, U48.22
PIO25: JP97.1, R225.2, U50.22
PIO26: JP101.1, R234.2, U52.22
PIO27: JP105.1, R243.2, U54.22
PIO28: JP109.1, R252.2, U56.22
PIO29: JP113.1, R261.2, U58.22
PIO30: JP117.1, R270.2, U60.22
PIO31: JP121.1, R279.2, U62.22
PIO32: JP125.1, R288.2, U64.22
PIO33: JP129.1, R297.2, U66.22
PIO34: JP133.1, R306.2, U68.22
PIO35: JP137.1, R315.2, U70.22
PIO36: JP141.1, R324.2, U72.22
PIO37: JP145.1, R333.2, U74.22
PIO38: JP149.1, R342.2, U76.22
PIO39: JP153.1, R351.2, U78.22
PIO40: JP157.1, R360.2, U80.22
PIO41: JP161.1, R369.2, U82.22
PIO42: JP165.1, R378.2, U84.22
PIO43: JP169.1, R387.2, U86.22
PIO44: JP173.1, R396.2, U88.22
PIO45: JP177.1, R405.2, U90.22
PIO46: JP181.1, R414.2, U92.22
PIO47: JP185.1, R423.2, U94.22
PIO48: JP189.1, R432.2, U96.22
RTS: Q2.2, R7.2, SJ1.1, U1.15
RTS1: Q3.2, R11.2, SJ2.1, U4.15
RTS2: Q5.2, R20.2, SJ3.1, U6.15
RTS3: Q7.2, R29.2, SJ4.1, U8.15
RTS4: Q9.2, R38.2, SJ5.1, U10.15
RTS5: Q11.2, R47.2, SJ6.1, U12.15
RTS6: Q13.2, R56.2, SJ7.1, U14.15
RTS7: Q15.2, R65.2, SJ8.1, U16.15
RTS8: Q17.2, R74.2, SJ9.1, U18.15
RTS9: Q19.2, R83.2, SJ10.1, U20.15
RTS10: Q21.2, R92.2, SJ11.1, U22.15
RTS11: Q23.2, R101.2, SJ12.1, U24.15
RTS12: Q25.2, R110.2, SJ13.1, U26.15
RTS13: Q27.2, R119.2, SJ14.1, U28.15
RTS14: Q29.2, R128.2, SJ15.1, U30.15
RTS15: Q31.2, R137.2, SJ16.1, U32.15
RTS16: Q33.2, R146.2, SJ17.1, U34.15
RTS17: Q35.2, R155.2, SJ18.1, U36.15
RTS18: Q37.2, R164.2, SJ19.1, U38.15
RTS19: Q39.2, R173.2, SJ20.1, U40.15
RTS20: Q41.2, R182.2, SJ21.1, U42.15
RTS21: Q43.2, R191.2, SJ22.1, U44.15
RTS22: Q45.2, R200.2, SJ23.1, U46.15
RTS23: Q47.2, R209.2, SJ24.1, U48.15
RTS24: Q49.2, R218.2, SJ25.1, U50.15
RTS25: Q51.2, R227.2, SJ26.1, U52.15
RTS26: Q53.2, R236.2, SJ27.1, U54.15
RTS27: Q55.2, R245.2, SJ28.1, U56.15
RTS28: Q57.2, R254.2, SJ29.1, U58.15
RTS29: Q59.2, R263.2, SJ30.1, U60.15
RTS30: Q61.2, R272.2, SJ31.1, U62.15
RTS31: Q63.2, R281.2, SJ32.1, U64.15
RTS32: Q65.2, R290.2, SJ33.1, U66.15
RTS33: Q67.2, R299.2, SJ34.1, U68.15
RTS34: Q69.2, R308.2, SJ35.1, U70.15
RTS35: Q71.2, R317.2, SJ36.1, U72.15
RTS36: Q73.2, R326.2, SJ37.1, U74.15
RTS37: Q75.2, R335.2, SJ38.1, U76.15
RTS38: Q77.2, R344.2, SJ39.1, U78.15
RTS39: Q79.2, R353.2, SJ40.1, U80.15
RTS40: Q81.2, R362.2, SJ41.1, U82.15
RTS41: Q83.2, R371.2, SJ42.1, U84.15
RTS42: Q85.2, R380.2, SJ43.1, U86.15
RTS43: Q87.2, R389.2, SJ44.1, U88.15
RTS44: Q89.2, R398.2, SJ45.1, U90.15
RTS45: Q91.2, R407.2, SJ46.1, U92.15
RTS46: Q93.2, R416.2, SJ47.1, U94.15
RTS47: Q95.2, R425.2, SJ48.1, U96.15
RTS_5V: JP3.1, Q2.3, R8.2
RTS_5V1: JP6.1, Q3.3, R12.2
RTS_5V2: JP10.1, Q5.3, R21.2
RTS_5V3: JP14.1, Q7.3, R30.2
RTS_5V4: JP18.1, Q9.3, R39.2
RTS_5V5: JP22.1, Q11.3, R48.2
RTS_5V6: JP26.1, Q13.3, R57.2
RTS_5V7: JP30.1, Q15.3, R66.2
RTS_5V8: JP34.1, Q17.3, R75.2
RTS_5V9: JP38.1, Q19.3, R84.2
RTS_5V10: JP42.1, Q21.3, R93.2
RTS_5V11: JP46.1, Q23.3, R102.2
RTS_5V12: JP50.1, Q25.3, R111.2
RTS_5V13: JP54.1, Q27.3, R120.2
RTS_5V14: JP58.1, Q29.3, R129.2
RTS_5V15: JP62.1, Q31.3, R138.2
RTS_5V16: JP66.1, Q33.3, R147.2
RTS_5V17: JP70.1, Q35.3, R156.2
RTS_5V18: JP74.1, Q37.3, R165.2
RTS_5V19: JP78.1, Q39.3, R174.2
RTS_5V20: JP82.1, Q41.3, R183.2
RTS_5V21: JP86.1, Q43.3, R192.2
RTS_5V22: JP90.1, Q45.3, R201.2
RTS_5V23: JP94.1, Q47.3, R210.2
RTS_5V24: JP98.1, Q49.3, R219.2
RTS_5V25: JP102.1, Q51.3, R228.2
RTS_5V26: JP106.1, Q53.3, R237.2
RTS_5V27: JP110.1, Q55.3, R246.2
RTS_5V28: JP114.1, Q57.3, R255.2
RTS_5V29: JP118.1, Q59.3, R264.2
RTS_5V30: JP122.1, Q61.3, R273.2
RTS_5V31: JP126.1, Q63.3, R282.2
RTS_5V32: JP130.1, Q65.3, R291.2
RTS_5V33: JP134.1, Q67.3, R300.2
RTS_5V34: JP138.1, Q69.3, R309.2
RTS_5V35: JP142.1, Q71.3, R318.2
RTS_5V36: JP146.1, Q73.3, R327.2
RTS_5V37: JP150.1, Q75.3, R336.2
RTS_5V38: JP154.1, Q77.3, R345.2
RTS_5V39: JP158.1, Q79.3, R354.2
RTS_5V40: JP162.1, Q81.3, R363.2
RTS_5V41: JP166.1, Q83.3, R372.2
RTS_5V42: JP170.1, Q85.3, R381.2
RTS_5V43: JP174.1, Q87.3, R390.2
RTS_5V44: JP178.1, Q89.3, R399.2
RTS_5V45: JP182.1, Q91.3, R408.2
RTS_5V46: JP186.1, Q93.3, R417.2
RTS_5V47: JP190.1, Q95.3, R426.2
RX: R5.1, U1.13
RX1: R16.1, U4.13
RX2: R25.1, U6.13
RX3: R34.1, U8.13
RX4: R43.1, U10.13
RX5: R52.1, U12.13
RX6: R61.1, U14.13
RX7: R70.1, U16.13
RX8: R79.1, U18.13
RX9: R88.1, U20.13
RX10: R97.1, U22.13
RX11: R106.1, U24.13
RX12: R115.1, U26.13
RX13: R124.1, U28.13
RX14: R133.1, U30.13
RX15: R142.1, U32.13
RX16: R151.1, U34.13
RX17: R160.1, U36.13
RX18: R169.1, U38.13
RX19: R178.1, U40.13
RX20: R187.1, U42.13
RX21: R196.1, U44.13
RX22: R205.1, U46.13
RX23: R214.1, U48.13
RX24: R223.1, U50.13
RX25: R232.1, U52.13
RX26: R241.1, U54.13
RX27: R250.1, U56.13
RX28: R259.1, U58.13
RX29: R268.1, U60.13
RX30: R277.1, U62.13
RX31: R286.1, U64.13
RX32: R295.1, U66.13
RX33: R304.1, U68.13
RX34: R313.1, U70.13
RX35: R322.1, U72.13
RX36: R331.1, U74.13
RX37: R340.1, U76.13
RX38: R349.1, U78.13
RX39: R358.1, U80.13
RX40: R367.1, U82.13
RX41: R376.1, U84.13
RX42: R385.1, U86.13
RX43: R394.1, U88.13
RX44: R403.1, U90.13
RX45: R412.1, U92.13
RX46: R421.1, U94.13
RX47: R430.1, U96.13
RX_5V: JP3.2, R5.2
RX_5V1: JP6.2, R16.2
RX_5V2: JP10.2, R25.2
RX_5V3: JP14.2, R34.2
RX_5V4: JP18.2, R43.2
RX_5V5: JP22.2, R52.2
RX_5V6: JP26.2, R61.2
RX_5V7: JP30.2, R70.2
RX_5V8: JP34.2, R79.2
RX_5V9: JP38.2, R88.2
RX_5V10: JP42.2, R97.2
RX_5V11: JP46.2, R106.2
RX_5V12: JP50.2, R115.2
RX_5V13: JP54.2, R124.2
RX_5V14: JP58.2, R133.2
RX_5V15: JP62.2, R142.2
RX_5V16: JP66.2, R151.2
RX_5V17: JP70.2, R160.2
RX_5V18: JP74.2, R169.2
RX_5V19: JP78.2, R178.2
RX_5V20: JP82.2, R187.2
RX_5V21: JP86.2, R196.2
RX_5V22: JP90.2, R205.2
RX_5V23: JP94.2, R214.2
RX_5V24: JP98.2, R223.2
RX_5V25: JP102.2, R232.2
RX_5V26: JP106.2, R241.2
RX_5V27: JP110.2, R250.2
RX_5V28: JP114.2, R259.2
RX_5V29: JP118.2, R268.2
RX_5V30: JP122.2, R277.2
RX_5V31: JP126.2, R286.2
RX_5V32: JP130.2, R295.2
RX_5V33: JP134.2, R304.2
RX_5V34: JP138.2, R313.2
RX_5V35: JP142.2, R322.2
RX_5V36: JP146.2, R331.2
RX_5V37: JP150.2, R340.2
RX_5V38: JP154.2, R349.2
RX_5V39: JP158.2, R358.2
RX_5V40: JP162.2, R367.2
RX_5V41: JP166.2, R376.2
RX_5V42: JP170.2, R385.2
RX_5V43: JP174.2, R394.2
RX_5V44: JP178.2, R403.2
RX_5V45: JP182.2, R412.2
RX_5V46: JP186.2, R421.2
RX_5V47: JP190.2, R430.2
TX: Q1.2, R3.2, U1.14
TX1: Q4.2, R14.2, U4.14
TX2: Q6.2, R23.2, U6.14
TX3: Q8.2, R32.2, U8.14
TX4: Q10.2, R41.2, U10.14
TX5: Q12.2, R50.2, U12.14
TX6: Q14.2, R59.2, U14.14
TX7: Q16.2, R68.2, U16.14
TX8: Q18.2, R77.2, U18.14
TX9: Q20.2, R86.2, U20.14
TX10: Q22.2, R95.2, U22.14
TX11: Q24.2, R104.2, U24.14
TX12: Q26.2, R113.2, U26.14
TX13: Q28.2, R122.2, U28.14
TX14: Q30.2, R131.2, U30.14
TX15: Q32.2, R140.2, U32.14
TX16: Q34.2, R149.2, U34.14
TX17: Q36.2, R158.2, U36.14
TX18: Q38.2, R167.2, U38.14
TX19: Q40.2, R176.2, U40.14
TX20: Q42.2, R185.2, U42.14
TX21: Q44.2, R194.2, U44.14
TX22: Q46.2, R203.2, U46.14
TX23: Q48.2, R212.2, U48.14
TX24: Q50.2, R221.2, U50.14
TX25: Q52.2, R230.2, U52.14
TX26: Q54.2, R239.2, U54.14
TX27: Q56.2, R248.2, U56.14
TX28: Q58.2, R257.2, U58.14
TX29: Q60.2, R266.2, U60.14
TX30: Q62.2, R275.2, U62.14
TX31: Q64.2, R284.2, U64.14
TX32: Q66.2, R293.2, U66.14
TX33: Q68.2, R302.2, U68.14
TX34: Q70.2, R311.2, U70.14
TX35: Q72.2, R320.2, U72.14
TX36: Q74.2, R329.2, U74.14
TX37: Q76.2, R338.2, U76.14
TX38: Q78.2, R347.2, U78.14
TX39: Q80.2, R356.2, U80.14
TX40: Q82.2, R365.2, U82.14
TX41: Q84.2, R374.2, U84.14
TX42: Q86.2, R383.2, U86.14
TX43: Q88.2, R392.2, U88.14
TX44: Q90.2, R401.2, U90.14
TX45: Q92.2, R410.2, U92.14
TX46: Q94.2, R419.2, U94.14
TX47: Q96.2, R428.2, U96.14
TX_5V: JP3.3, Q1.3, R4.2
TX_5V1: JP6.3, Q4.3, R15.2
TX_5V2: JP10.3, Q6.3, R24.2
TX_5V3: JP14.3, Q8.3, R33.2
TX_5V4: JP18.3, Q10.3, R42.2
TX_5V5: JP22.3, Q12.3, R51.2
TX_5V6: JP26.3, Q14.3, R60.2
TX_5V7: JP30.3, Q16.3, R69.2
TX_5V8: JP34.3, Q18.3, R78.2
TX_5V9: JP38.3, Q20.3, R87.2
TX_5V10: JP42.3, Q22.3, R96.2
TX_5V11: JP46.3, Q24.3, R105.2
TX_5V12: JP50.3, Q26.3, R114.2
TX_5V13: JP54.3, Q28.3, R123.2
TX_5V14: JP58.3, Q30.3, R132.2
TX_5V15: JP62.3, Q32.3, R141.2
TX_5V16: JP66.3, Q34.3, R150.2
TX_5V17: JP70.3, Q36.3, R159.2
TX_5V18: JP74.3, Q38.3, R168.2
TX_5V19: JP78.3, Q40.3, R177.2
TX_5V20: JP82.3, Q42.3, R186.2
TX_5V21: JP86.3, Q44.3, R195.2
TX_5V22: JP90.3, Q46.3, R204.2
TX_5V23: JP94.3, Q48.3, R213.2
TX_5V24: JP98.3, Q50.3, R222.2
TX_5V25: JP102.3, Q52.3, R231.2
TX_5V26: JP106.3, Q54.3, R240.2
TX_5V27: JP110.3, Q56.3, R249.2
TX_5V28: JP114.3, Q58.3, R258.2
TX_5V29: JP118.3, Q60.3, R267.2
TX_5V30: JP122.3, Q62.3, R276.2
TX_5V31: JP126.3, Q64.3, R285.2
TX_5V32: JP130.3, Q66.3, R294.2
TX_5V33: JP134.3, Q68.3, R303.2
TX_5V34: JP138.3, Q70.3, R312.2
TX_5V35: JP142.3, Q72.3, R321.2
TX_5V36: JP146.3, Q74.3, R330.2
TX_5V37: JP150.3, Q76.3, R339.2
TX_5V38: JP154.3, Q78.3, R348.2
TX_5V39: JP158.3, Q80.3, R357.2
TX_5V40: JP162.3, Q82.3, R366.2
TX_5V41: JP166.3, Q84.3, R375.2
TX_5V42: JP170.3, Q86.3, R384.2
TX_5V43: JP174.3, Q88.3, R393.2
TX_5V44: JP178.3, Q90.3, R402.2
TX_5V45: JP182.3, Q92.3, R411.2
TX_5V46: JP186.3, Q94.3, R420.2
TX_5V47: JP190.3, Q96.3, R429.2
VCC: C1.A, JP3.4, R4.1, R8.1, U3.1, U3.3
VCC1: C5.A, JP6.4, R12.1, R15.1, U2.1, U2.3
VCC2: C8.A, JP10.4, R21.1, R24.1, U5.1, U5.3
VCC3: C11.A, JP14.4, R30.1, R33.1, U7.1, U7.3
VCC4: C14.A, JP18.4, R39.1, R42.1, U9.1, U9.3
VCC5: C17.A, JP22.4, R48.1, R51.1, U11.1, U11.3
VCC6: C20.A, JP26.4, R57.1, R60.1, U13.1, U13.3
VCC7: C23.A, JP30.4, R66.1, R69.1, U15.1, U15.3
VCC8: C26.A, JP34.4, R75.1, R78.1, U17.1, U17.3
VCC9: C29.A, JP38.4, R84.1, R87.1, U19.1, U19.3
VCC10: C32.A, JP42.4, R93.1, R96.1, U21.1, U21.3
VCC11: C35.A, JP46.4, R102.1, R105.1, U23.1, U23.3
VCC12: C38.A, JP50.4, R111.1, R114.1, U25.1, U25.3
VCC13: C41.A, JP54.4, R120.1, R123.1, U27.1, U27.3
VCC14: C44.A, JP58.4, R129.1, R132.1, U29.1, U29.3
VCC15: C47.A, JP62.4, R138.1, R141.1, U31.1, U31.3
VCC16: C50.A, JP66.4, R147.1, R150.1, U33.1, U33.3
VCC17: C53.A, JP70.4, R156.1, R159.1, U35.1, U35.3
VCC18: C56.A, JP74.4, R165.1, R168.1, U37.1, U37.3
VCC19: C59.A, JP78.4, R174.1, R177.1, U39.1, U39.3
VCC20: C62.A, JP82.4, R183.1, R186.1, U41.1, U41.3
VCC21: C65.A, JP86.4, R192.1, R195.1, U43.1, U43.3
VCC22: C68.A, JP90.4, R201.1, R204.1, U45.1, U45.3
VCC23: C71.A, JP94.4, R210.1, R213.1, U47.1, U47.3
VCC24: C74.A, JP98.4, R219.1, R222.1, U49.1, U49.3
VCC25: C77.A, JP102.4, R228.1, R231.1, U51.1, U51.3
VCC26: C80.A, JP106.4, R237.1, R240.1, U53.1, U53.3
VCC27: C83.A, JP110.4, R246.1, R249.1, U55.1, U55.3
VCC28: C86.A, JP114.4, R255.1, R258.1, U57.1, U57.3
VCC29: C89.A, JP118.4, R264.1, R267.1, U59.1, U59.3
VCC30: C92.A, JP122.4, R273.1, R276.1, U61.1, U61.3
VCC31: C95.A, JP126.4, R282.1, R285.1, U63.1, U63.3
VCC32: C98.A, JP130.4, R291.1, R294.1, U65.1, U65.3
VCC33: C101.A, JP134.4, R300.1, R303.1, U67.1, U67.3
VCC34: C104.A, JP138.4, R309.1, R312.1, U69.1, U69.3
VCC35: C107.A, JP142.4, R318.1, R321.1, U71.1, U71.3
VCC36: C110.A, JP146.4, R327.1, R330.1, U73.1, U73.3
VCC37: C113.A, JP150.4, R336.1, R339.1, U75.1, U75.3
VCC38: C116.A, JP154.4, R345.1, R348.1, U77.1, U77.3
VCC39: C119.A, JP158.4, R354.1, R357.1, U79.1, U79.3
VCC40: C122.A, JP162.4, R363.1, R366.1, U81.1, U81.3
VCC41: C125.A, JP166.4, R372.1, R375.1, U83.1, U83.3
VCC42: C128.A, JP170.4, R381.1, R384.1, U85.1, U85.3
VCC43: C131.A, JP174.4, R390.1, R393.1, U87.1, U87.3
VCC44: C134.A, JP178.4, R399.1, R402.1, U89.1, U89.3
VCC45: C137.A, JP182.4, R408.1, R411.1, U91.1, U91.3
VCC46: C140.A, JP186.4, R417.1, R420.1, U93.1, U93.3
VCC47: C143.A, JP190.4, R426.1, R429.1, U95.1, U95.3

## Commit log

2013-06-05 Initial board file commit with updated RN-41 footprint
2013-07-05 Updated Caps/Res to 0603 packages
2013-07-08 Additional updates to layout
2013-07-09 Fixed additional layout issues
2013-07-11 Fix PIO6 label to PIO4
2013-07-17 Fix silk screen/symbol errors
2013-07-17 Created panels
    created giant panel and smaller manncorp panel
2013-07-17 added version number to production files
2013-10-01 Added 2nd fiducial
    Production files updated to v16a
    Hardware files updated also
2014-02-06 Updating new part numbers in README
2014-07-29 Add Fritzing files
2014-08-18 Fritzing stuff
